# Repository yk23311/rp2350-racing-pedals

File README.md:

# 基于 RP2350 的赛车模拟器油门与刹车

**嘉立创打样资料**包括 [Gerber ZIP](hardware/jlc-v0.1/01-PCB-Gerber-RS274X.zip)、[SMT BOM](hardware/jlc-v0.1/02-BOM-SMT.csv)、[贴装坐标](hardware/jlc-v0.1/03-CPL-SMT.csv)和[下单说明](hardware/jlc-v0.1/README.md)。

**可扩展接线底板 V0.1**预留四路模拟端子、16 键、I²C 屏幕、面板编码器、震动控制和直驱接口子板槽。源码与针脚说明见 [KiCad 工程](hardware/carrier/README.md)，手焊见[材料清单、焊接手册和分区图](hardware/carrier-assembly-v0.1/README.md)。实板已用于双踏板测试，扩展接口仍需固件适配和上板验收。

**下载：[v0.4.0 预发布版](https://github.com/yk23311/rp2350-racing-pedals/releases/tag/v0.4.0)**，包含普通/诊断UF2、含GUI的源码包、快速说明与SHA256。软件测试通过，仍待实机验收；GUI源码包需Python环境。

**当前源码 0.6.0**支持 J1/J2 油门刹车互换、Xbox 桥接与原生 HID 方向盘切换，以及按键测试、震动测试和一键升级。Windows 已验证实板的三个独立方向盘轴，《地平线 6》的自定义方向盘布局保存仍待验证。 [操作与验证记录](docs/reports/25-simulator-wheel-handoff.md)

**新版驾驶控制中心已实现**：自动识别串口，实时踏板百分比、手柄按键/摇杆/扳机监视，踏板和手柄曲线预览与调参，手柄按钮→手柄/键盘映射。双击根目录 **启动调参GUI.bat**，详见[一步步使用说明](docs/control-center.md)。

按下文构建桥接固件，产物为 `dist/host/pedals-host.uf2`。Type-C 接电脑，2.4G 接收器插板卡 USB-A，踏板接底板 J1/J2。曲线和映射由板端执行，关闭 GUI 后仍有效。

旧固件可继续调踏板；手柄遥测和配置会明确显示不支持。新固件能迁移读取旧PDL1校准；显式保存后使用PDL2，旧固件不能读取新格式，降级前请备份校准。下文旧HID/Tk内容作为历史与兼容路线保留，最新入口为[HANDOFF.md](HANDOFF.md)。

**当前传感器仅确认 5V 供电，输出类型和电压未知。先按 [硬件接入说明](docs/hardware.md) 测量，不能直接把未知信号接到 GP26/GP27。** 未校准默认输出中立。

## 从 GitHub 首次使用

本仓库包含源码、测试、文档与界面演示图，不上传本地工具链、`.venv`、`build`、`deps`或`dist`。面向Windows与微雪RP2350-USB-A开发板；没有硬件也能预览GUI。

```powershell
python -m venv .venv
.\.venv\Scripts\python.exe -m pip install -r tools/requirements.txt
powershell -ExecutionPolicy Bypass -File tools/start_gui.ps1 -Demo
```

实际连接时去掉`-Demo`。先按下文构建桥接固件；旧固件首次需手动BOOT安装，此后可在GUI“固件升级”选择UF2并点击自动升级。GUI不会在后台自行刷机。界面如下（演示数据）：

## 工程入口

- [方案审核与来源](docs/reports/01-review.md)
- [首版设计](docs/superpowers/specs/2026-10-30-pedals-design.md) / [实施计划](docs/superpowers/plans/2026-10-30-pedals-plan.md)
- [步骤及交接报告总表](docs/reports/00-handoff.md)
- [硬件说明](docs/hardware.md) / [验收步骤](docs/validation.md) / [CDC协议](docs/protocol.md)

目录：`src/core/` 纯C算法、记录格式、控制台、USB报告布局与中立屏障；`firmware/` Pico HAL、Flash、TinyUSB、主循环；`tools/` 构建、CLI、GUI；`tests/` PC验证。

## 电脑端测试

Windows 已安装 Visual Studio C++/Clang、CMake、Ninja 和 Python 时：

```powershell
powershell -ExecutionPolicy Bypass -File tools/build_host.ps1
```

其他平台也可用原生C编译器运行：

```sh
cmake -S . -B build/host -DCMAKE_BUILD_TYPE=Release
cmake --build build/host
ctest --test-dir build/host --output-on-failure
python -m unittest discover -s tests -p 'test_*.py' -v
```

## 构建固件（Windows）

```powershell
python tools/fetch_deps.py
powershell -ExecutionPolicy Bypass -File tools/build_firmware.ps1 -UsbMode host
```

依赖只下载至项目 `deps/`：Pico SDK 2.2.0、其锁定的 TinyUSB、Arm GNU 14.3.rel1。下载较大；需要联网。脚本打印 SHA256 供记录，但不等于验证上游数字签名。桥接构建输出 `dist/host/pedals-host.*`；不传`-UsbMode host`时脚本仍默认构建独立踏板`dist/xinput/pedals-xinput.*`；`-UsbMode hid`输出 `dist/hid/pedals-hid.*`。UF2使用 SDK定义的 RP2350 ARM-S family，不自动烧录。

Windows Arm链接器在本项目中文路径下无法解析其标准库；脚本临时使用空闲R:映射本项目，完成或失败后移除。R:已被占用时可传入 `-DriveLetter S`；不会覆盖现有盘符，也不移动工程。构建缓存分为 `build/firmware-xinput-R/` 与 `build/firmware-hid-R/`。

Flash配置保留区：`0x101FE000` 和 `0x101FF000` 两个4KiB扇区；正常程序链接区不覆盖该区域。更新固件通常保留配置；整片擦除会清空。

## 上板后调参

项目已准备好独立的 `.venv` 串口环境；GUI 使用 Python 自带的 Tkinter，无需 PyQt。

**最简单的启动方式：双击项目根目录的 `启动调参GUI.bat`。** 也可以在 PowerShell 中运行：

```powershell
powershell -ExecutionPolicy Bypass -File tools/start_gui.ps1
```

只想检查环境而不打开窗口：

```powershell
powershell -ExecutionPolicy Bypass -File tools/start_gui.ps1 -Check
```

移交到新电脑时先执行 `python -m venv .venv`，再执行 `.\.venv\Scripts\python.exe -m pip install -r tools/requirements.txt`。CLI也使用该虚拟环境的Python；下列示例运行前可执行 `.\.venv\Scripts\Activate.ps1`，或把 `python` 换成 `.\.venv\Scripts\python.exe`。

输入设备管理器中确认的串口号。滑条调节后点“应用参数”在 RAM 生效；松开两踏板并回零后点“保存到 Flash”。两轴分别执行“全松开：开始校准”→“踩到底并保持：完成”，每个位置至少保持100ms再操作。

也可使用CLI（以下COM5仅作示例）：

```powershell
python tools/pedalctl.py --port COM5 get
python tools/pedalctl.py --port COM5 calibrate 0
python tools/pedalctl.py --port COM5 calibrate 1
python tools/pedalctl.py --port COM5 set 1 --on 300 --off 100 --gamma 200 --window 4
python tools/pedalctl.py --port COM5 save
python tools/pedalctl.py --port COM5 export pedal-config.json
python tools/pedalctl.py --port COM5 monitor --seconds 3600 --interval 0.1 --output aging.csv
```

`on/off`单位为万分之一（300=3%），`gamma`单位为百分之一（200=2.00）。`SAVE`返回状态错误时先松开两踏板、结束校准、等待中立报告完成再重试；不能视作已经保存。CSV为电脑轮询数据，默认10Hz，不是全部1kHz ADC样本。

## 已明确的限制

- 当前为开发验证版本；实机验收记录见交接总表。标准HID不等于XInput，按目标游戏验证兼容性。
- 开发 VID/PID 为 `CAFE:4011`，不作为正式分配的产品身份；发布硬件前需获得合适的USB身份并复验描述符。
- 固件声明最大100mA USB总电流，连接传感器前确认整板与传感器总需求；不在此供电预算内接电机。
- 方向盘模式支持输入。屏幕菜单、底板外置震动马达和伺服力反馈仍需适配。

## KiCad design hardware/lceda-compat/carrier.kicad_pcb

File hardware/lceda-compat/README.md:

# 嘉立创EDA网络兼容导入候选包

2026-11-07。这个目录仍是**用于导入的KiCad格式兼容副本，不是已生成的EDA原生eprj/epro工程**。原始 `hardware/carrier` 和已经核验的Gerber包保持不变。

## 为什么另做这个包

用户导出的`eda-import-diff.csv`表明：221个实际连接的引脚，在当前EDA PCB中导入前均显示为未指定网络；49个GND引脚在原理图侧被PWR_FLAG命名；另有15处元件值回填差异。原始KiCad10板图使用新版具名网络语法，旧式索引语法是本次兼容候选的验证方向。只显示铜线/DRC条数减少，不能证明网络导入成功。

## 副本中的兼容处理

- 所有844处网络关联写为旧式数字索引，补齐网络表；pad保留索引和原网名，segment/via/铜区引用索引，铜区增加net_name。**文件版本没有伪改为旧版。**
- 每个封装的Reference/Value属性使用兼容fp_text形式表达，保留各自数值、坐标、字体、隐藏状态和UUID。
- 仅移除原理图ERC专用PWR_FLAG及其独立标记支线/标签，从而避免EDA把这个声明当作地网名称；模块GND引脚的ERC类型从power_in调整为power_out，承担原来的供电声明，实体连接不变。本地模块符号库同步此纯ERC元数据变化。
- 581段走线、27个过孔、72个元件、238个焊盘、安装孔/禁布区和其他PCB几何均保留。

## 已完成的验证

- 原生KiCad读回全部元件/焊盘/走线/过孔，与原件逐项比较，几何/网络/实际值一致。
- 原生ERC：0违规；DRC：0违规、0未连接、0原理图一致性问题，使用同一原规则配置。
- 原生导出的原理图网表和原72元件电气模型逐脚一致。
- 九层Gerber的完整绘图流与原版完全一致；PTH/NPTH钻孔指令与原版一致。
- Python全套130项测试通过，其中6项为新增兼容合同测试。
- 独立复核反向还原全部PCB变换后，其完整S表达式结构与原版一致；符号/原理图只存在上述声明变化。

报告保存在`reports/`；诊断源报告UTF-16、制表符分隔，虽然后缀为CSV，不能按普通逗号CSV解析。

## 用户手动验证步骤

1. 在EDA专业版开始页选“导入KiCad”，选择`carrier-net-compat.zip`，导入为新工程。
2. 首次先查看PCB，不执行“导入更新”或重建铺铜。任选有连接的焊盘，查看网络属性是否已正确获得名字，例如C1.1为ADC_THROTTLE、C1.2为GND（显示时可能带层级前缀），R25应为4.7k、C7应为4.7µF。
3. 运行DRC并保留结果。如果仍有网表差异，只查看/导出差异报告，不盲目应用；报告中221项网络都从未指定开始的情况应先排除。
4. 确认原生网络已经保留后，再按实际错误匹配最小孔径0.30mm规则，并验证重建铺铜后铜线和连接状态仍保留。

**上述EDA实际导入、属性/网络保留、铺铜重建和EDA DRC均尚待用户验证。** 不得直接把本候选包作为已完成EDA验收的生产稿，不保证满足EDA专用优惠券资格。原始已核验Gerber仍是独立制造入口。

生成器为`tools/hardware/prepare_lceda_compat.py`，默认只生成副本；重新生成后必须重新运行原生检查和等价比对再打包，不沿用旧验证结论。

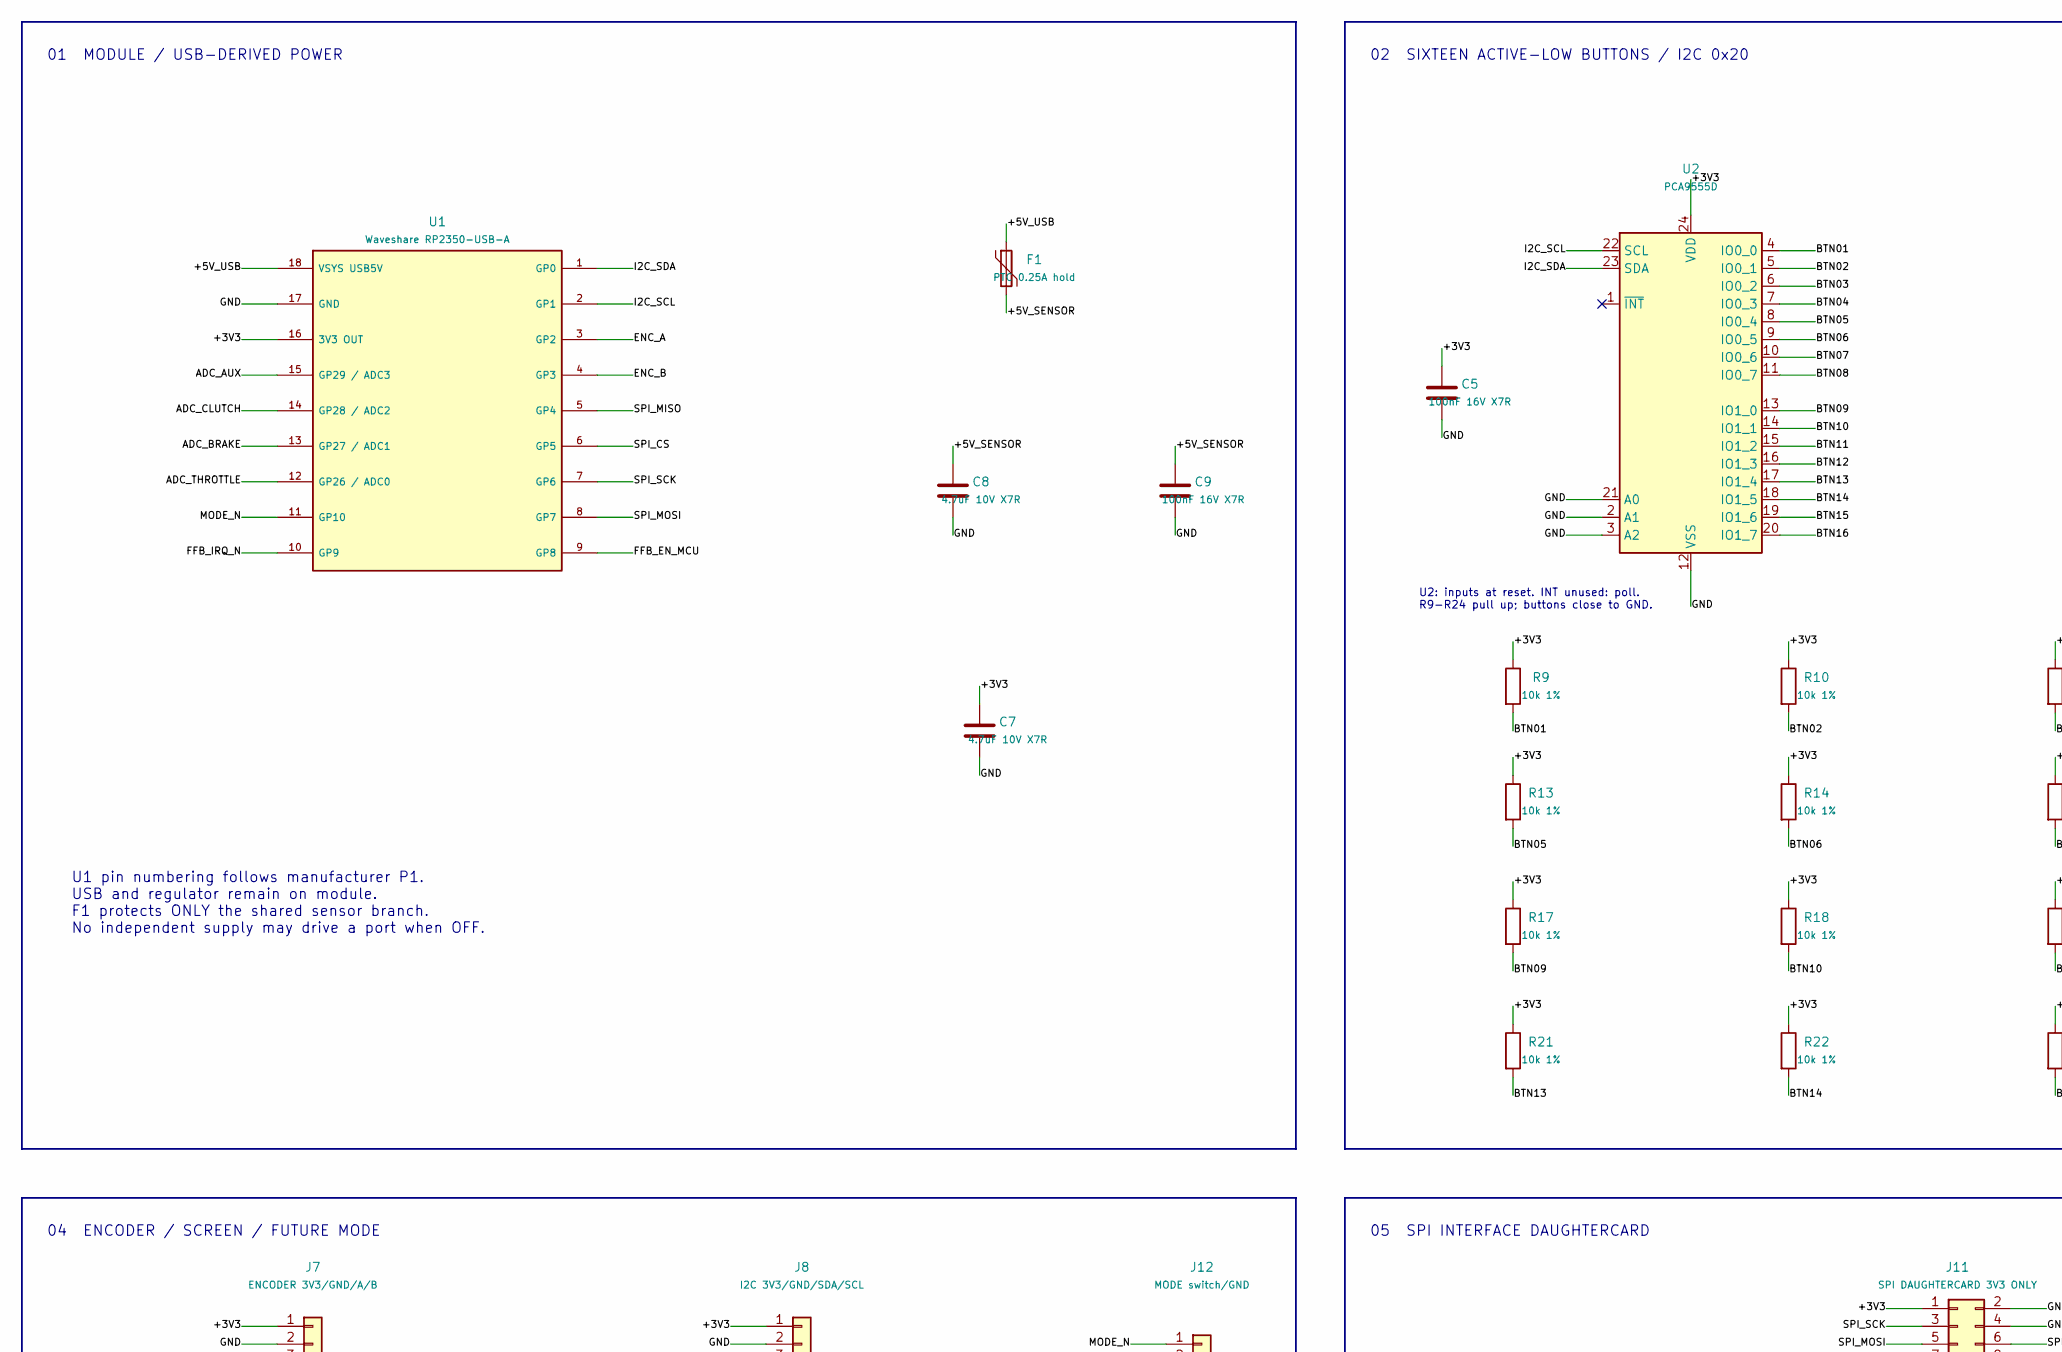
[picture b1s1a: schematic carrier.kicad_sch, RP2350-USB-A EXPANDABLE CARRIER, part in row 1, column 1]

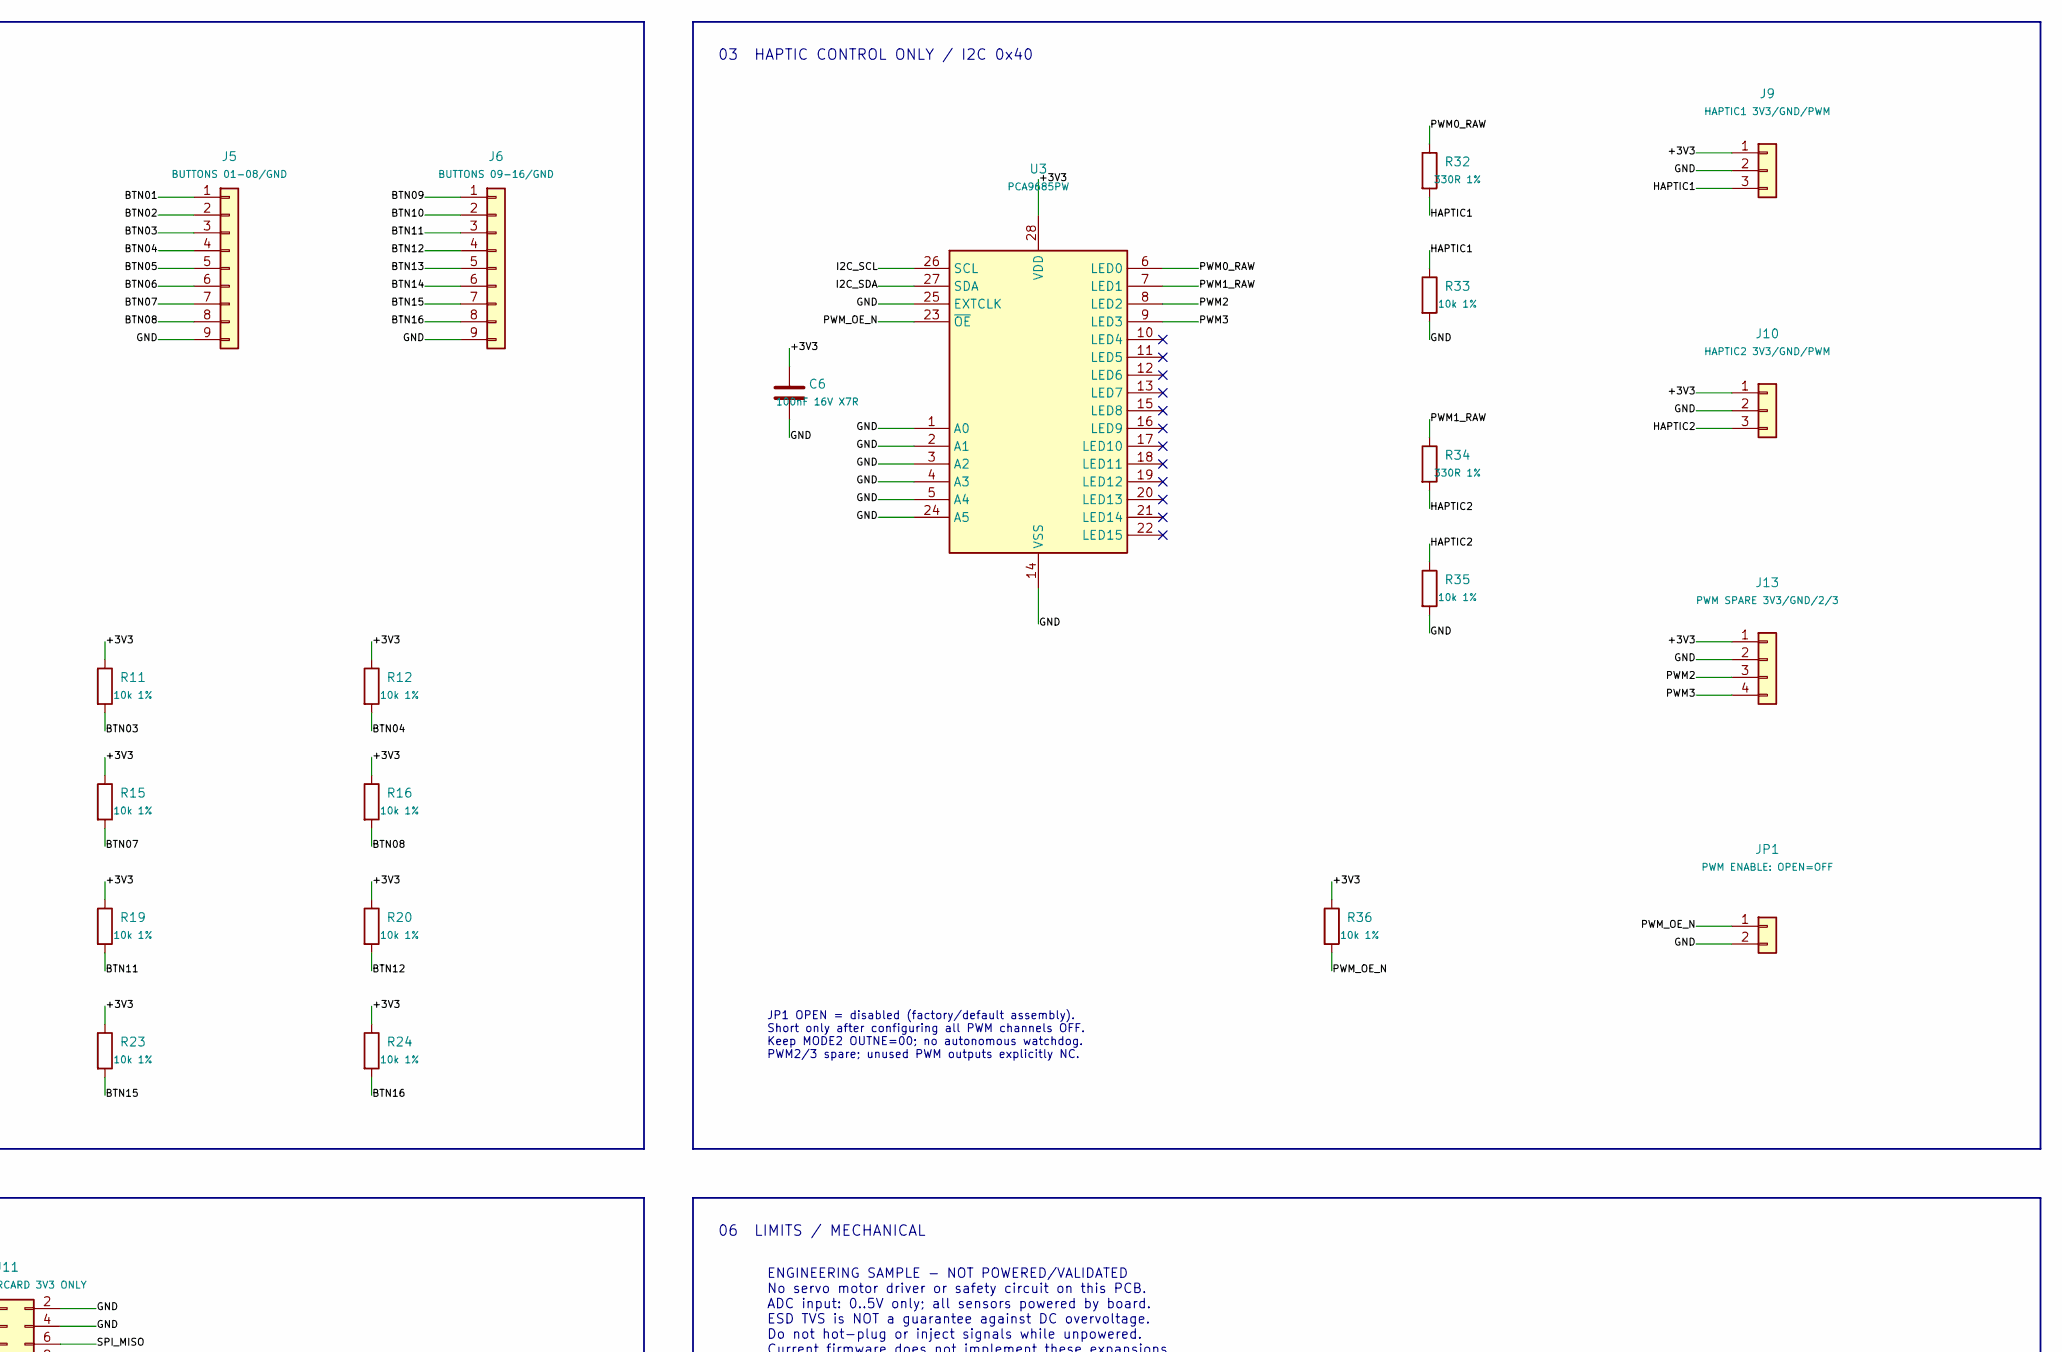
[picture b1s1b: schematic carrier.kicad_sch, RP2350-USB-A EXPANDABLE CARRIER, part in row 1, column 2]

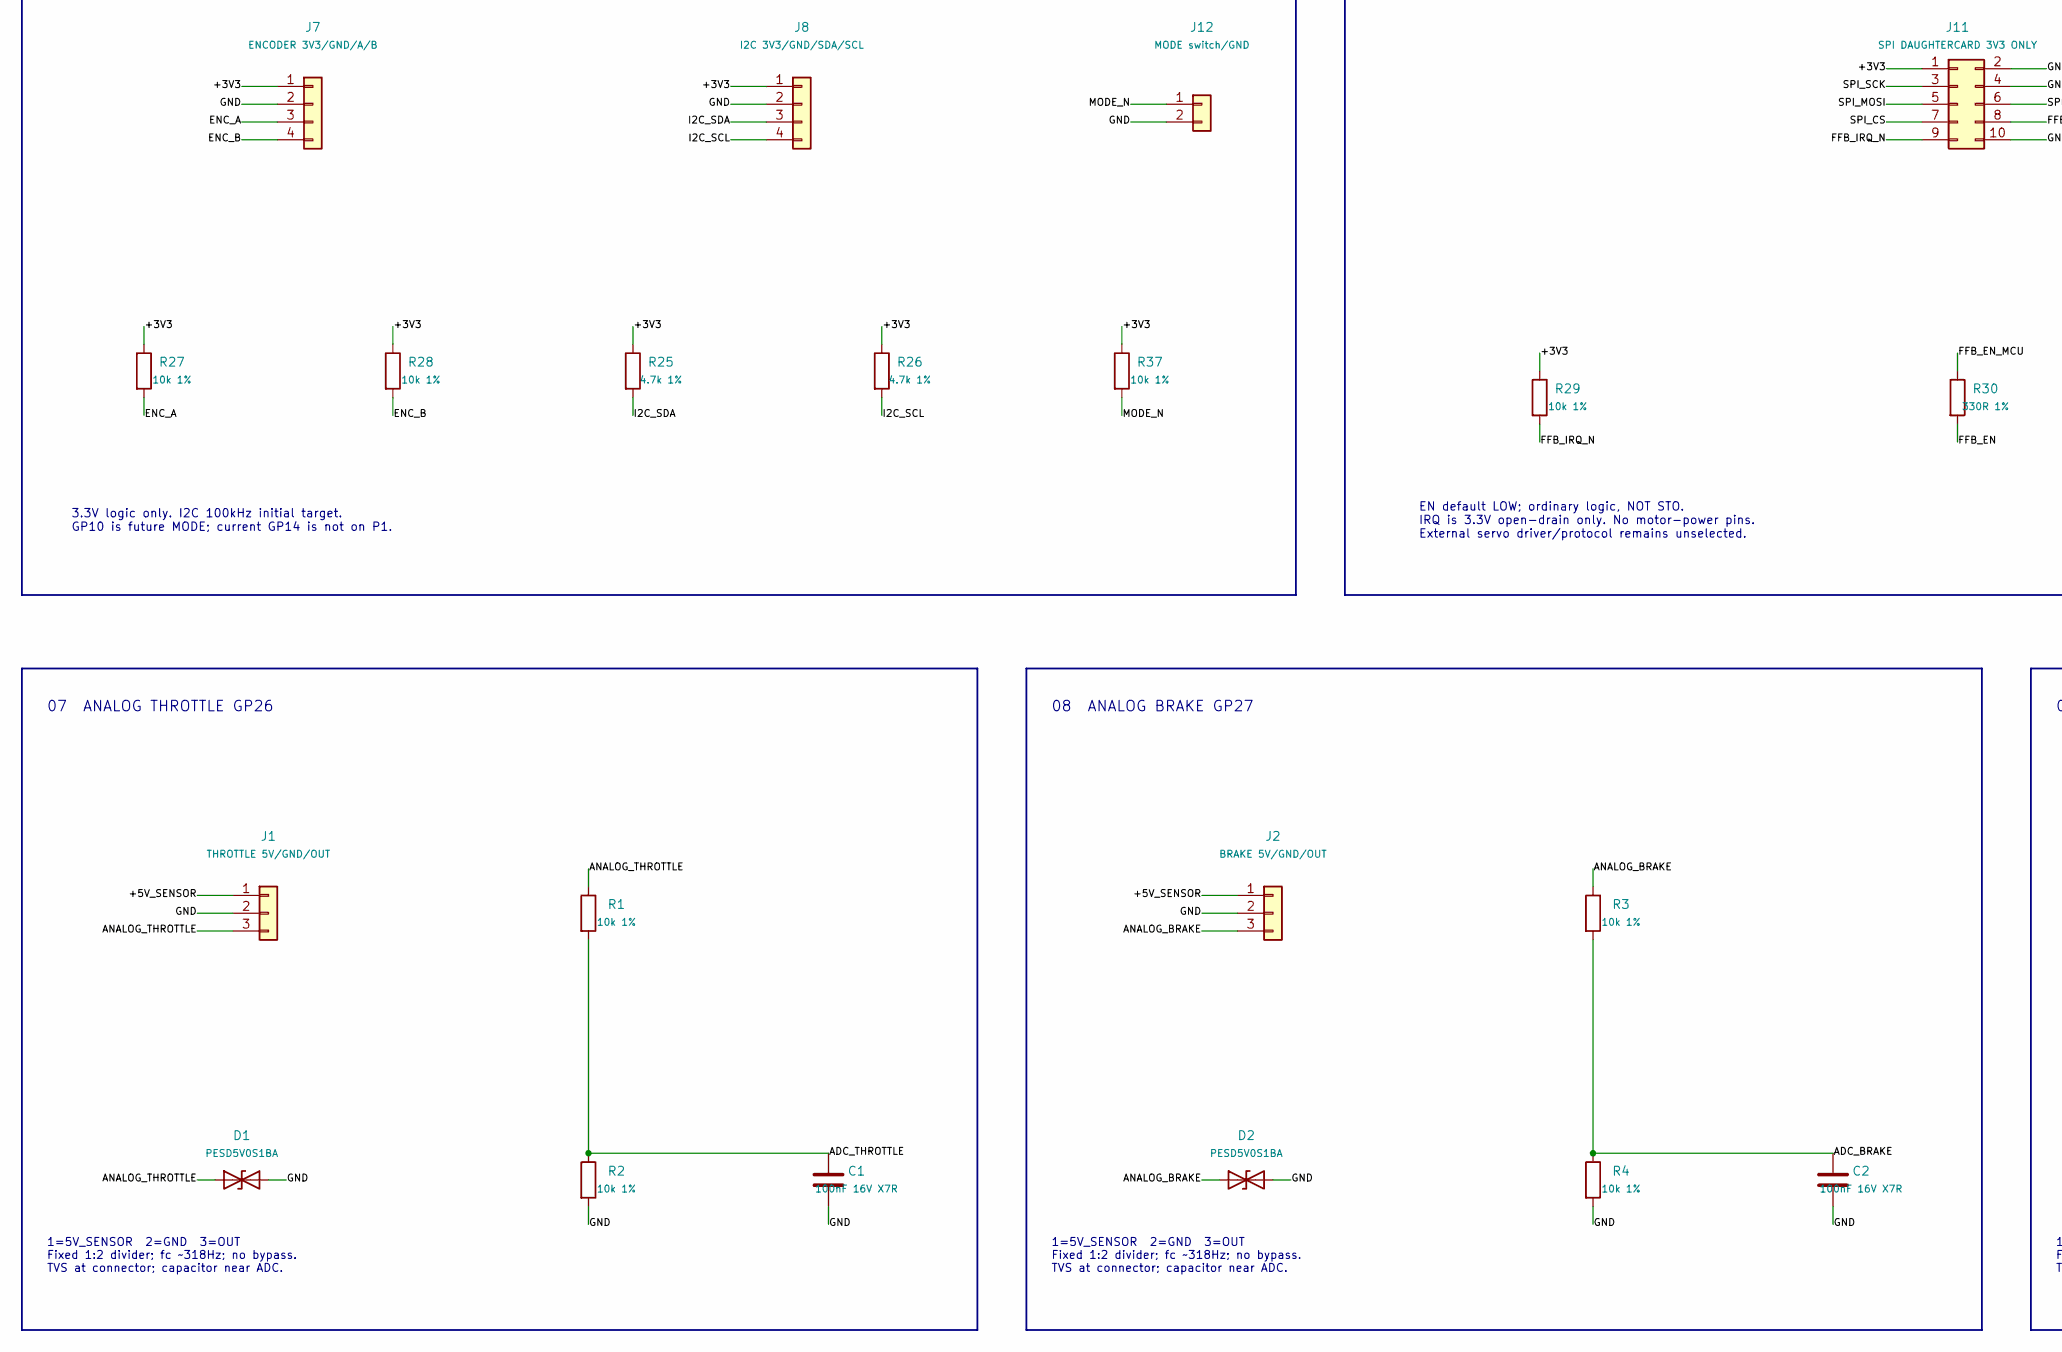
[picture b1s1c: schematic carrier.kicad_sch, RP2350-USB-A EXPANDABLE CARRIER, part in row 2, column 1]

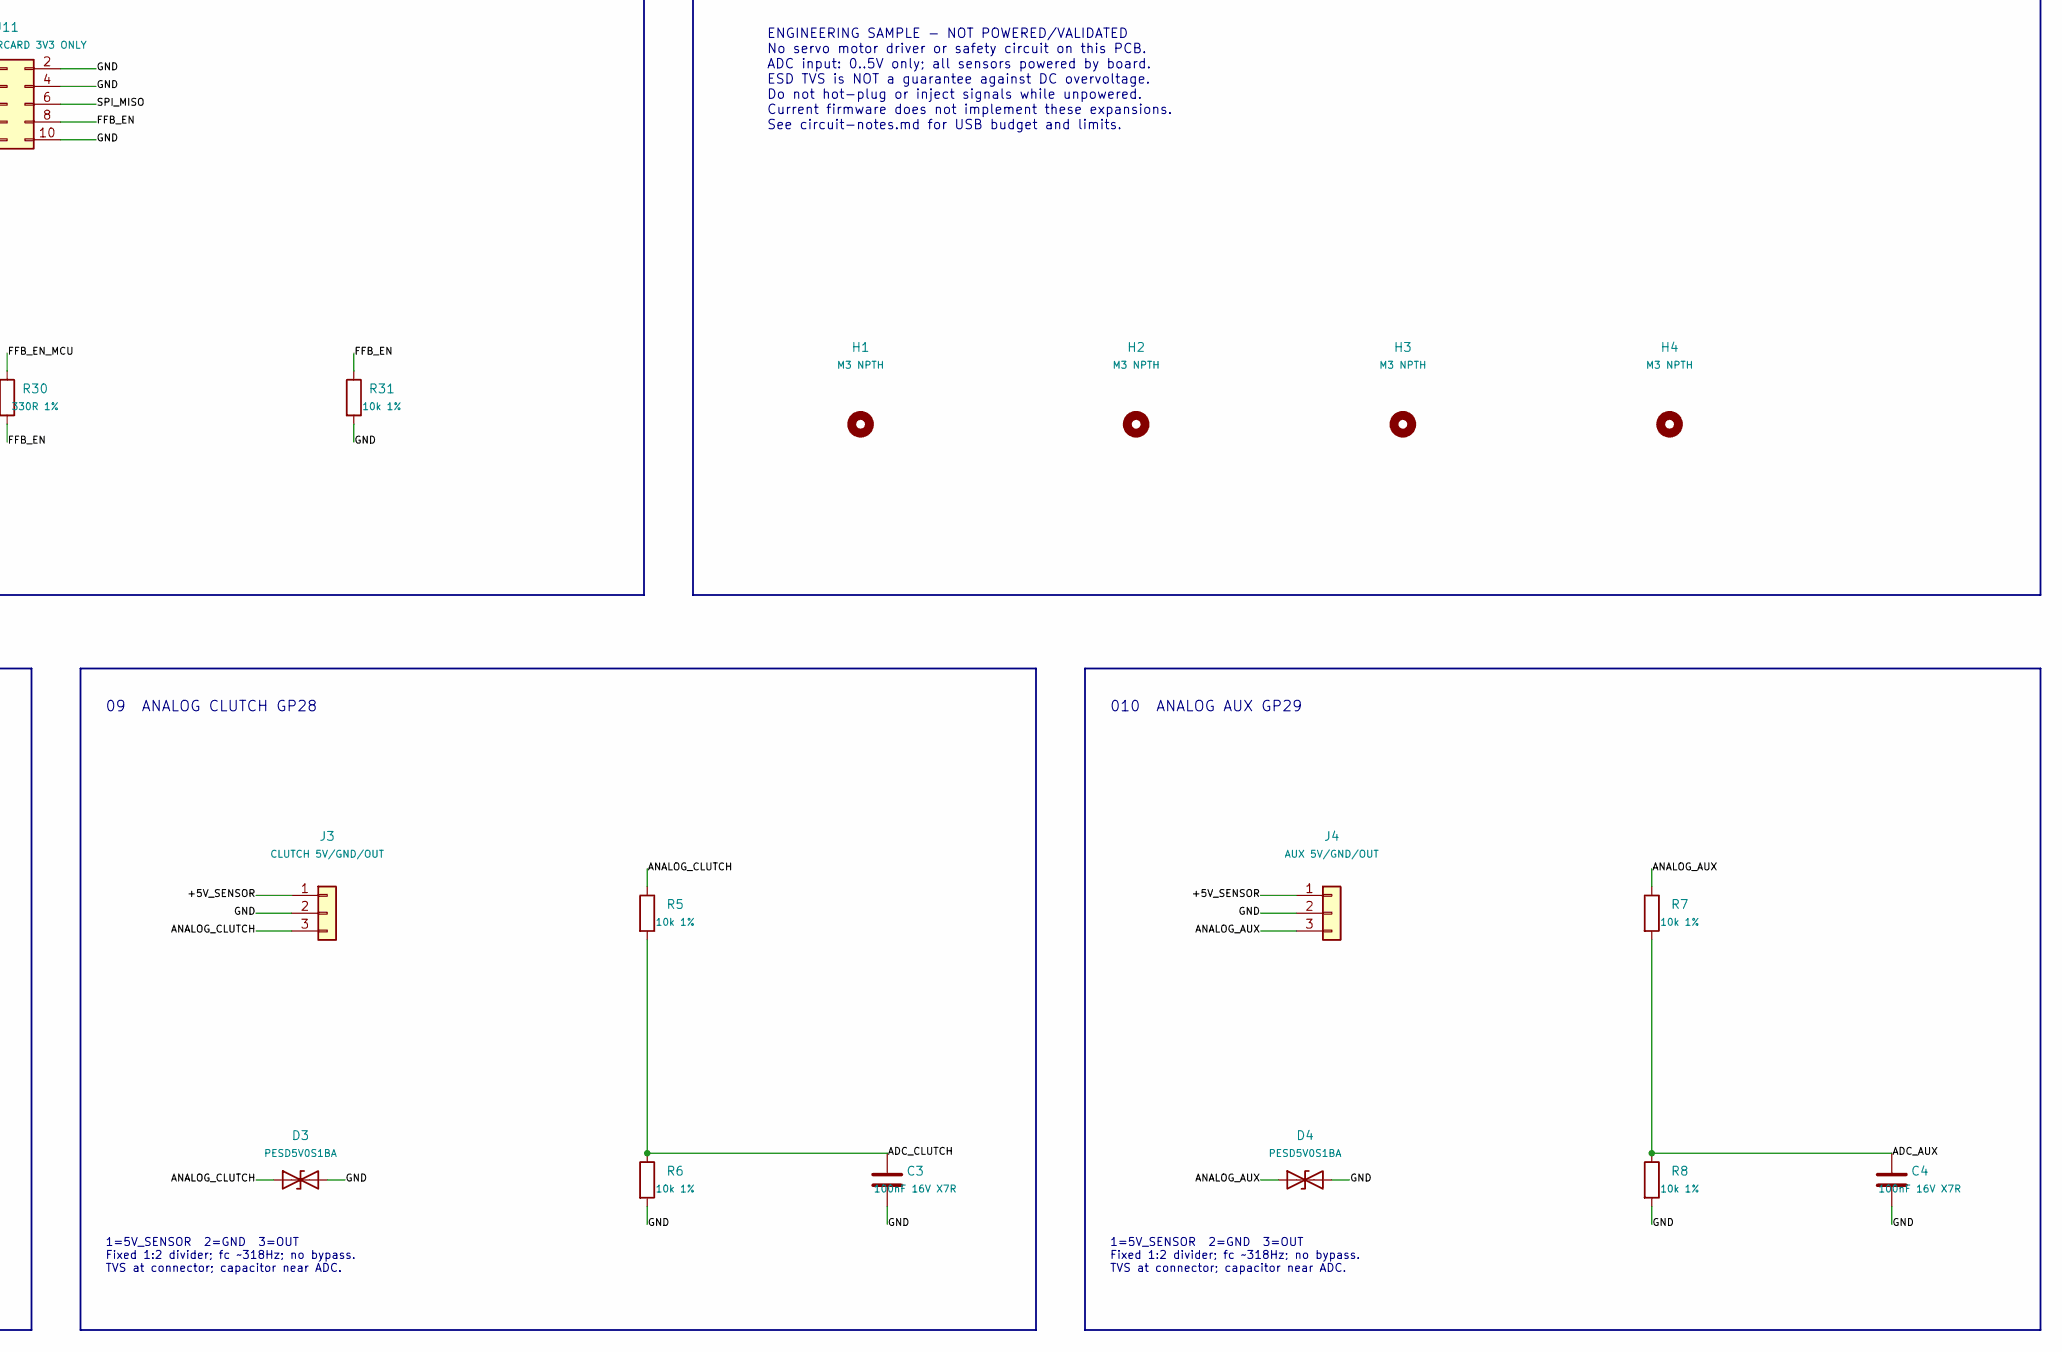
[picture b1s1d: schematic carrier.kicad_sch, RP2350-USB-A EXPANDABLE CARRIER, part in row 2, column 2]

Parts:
C1, C2, C3, C4, C5, C6, C9: 100nF 16V X7R; C_0805_2012Metric
C7, C8: 4.7uF 10V X7R; C_0805_2012Metric
D1, D2, D3, D4: PESD5V0S1BA; D_SOD-323
F1: PTC 0.25A hold; Fuse_1206_3216Metric
H1, H2, H3, H4: M3 NPTH; MountingHole_3.2mm_M3
J1: THROTTLE 5V/GND/OUT; TerminalBlock_Phoenix_MKDS-1,5-3-5.08_1x03_P5.08mm_Horizont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
J2: BRAKE 5V/GND/OUT; TerminalBlock_Phoenix_MKDS-1,5-3-5.08_1x03_P5.08mm_Horizont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
J3: CLUTCH 5V/GND/OUT; TerminalBlock_Phoenix_MKDS-1,5-3-5.08_1x03_P5.08mm_Horizont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
J4: AUX 5V/GND/OUT; TerminalBlock_Phoenix_MKDS-1,5-3-5.08_1x03_P5.08mm_Horizont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
J5: BUTTONS 01-08/GND; PinHeader_1x09_P2.54mm_Vertical
J6: BUTTONS 09-16/GND; PinHeader_1x09_P2.54mm_Vertical
J7: ENCODER 3V3/GND/A/B; PinHeader_1x04_P2.54mm_Vertical
J8: I2C 3V3/GND/SDA/SCL; PinHeader_1x04_P2.54mm_Vertical
J9: HAPTIC1 3V3/GND/PWM; PinHeader_1x03_P2.54mm_Vertical
J10: HAPTIC2 3V3/GND/PWM; PinHeader_1x03_P2.54mm_Vertical
J11: SPI DAUGHTERCARD 3V3 ONLY; PinHeader_2x05_P2.54mm_Vertical
J12: MODE switch/GND; PinHeader_1x02_P2.54mm_Vertical
J13: PWM SPARE 3V3/GND/2/3; PinHeader_1x04_P2.54mm_Vertical
JP1: PWM ENABLE: OPEN=OFF; PinHeader_1x02_P2.54mm_Vertical
R1, R2, R3, R4, R5, R6, R7, R8, R9, R10, R11, R12, R13, R14, R15, R16, R17, R18, R19, R20, R21, R22, R23, R24, R27, R28, R29, R31, R33, R35, R36, R37: 10k 1%; R_0805_2012Metric
R25, R26: 4.7k 1%; R_0805_2012Metric
R30, R32, R34: 330R 1%; R_0805_2012Metric
U1: Waveshare RP2350-USB-A; Waveshare_RP2350_USB_A
U2: PCA9555D; SOIC-24W_7.5x15.4mm_P1.27mm
U3: PCA9685PW; TSSOP-28_4.4x9.7mm_P0.65mm

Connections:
/+3V3: C5.1, C6.1, C7.1, J7.1, J8.1, J9.1, J10.1, J11.1, J13.1, R9.1, R10.1, R11.1, R12.1, R13.1, R14.1, R15.1, R16.1, R17.1, R18.1, R19.1, R20.1, R21.1, R22.1, R23.1, R24.1, R25.1, R26.1, R27.1, R28.1, R29.1, R36.1, R37.1, U1.16 (3V3 OUT), U2.24 (VDD), U3.28 (VDD)
/+5V_SENSOR: C8.1, C9.1, F1.2, J1.1, J2.1, J3.1, J4.1
/+5V_USB: F1.1, U1.18 (VSYS USB5V)
/ADC_AUX: C4.1, R7.2, R8.1, U1.15 (GP29 / ADC3)
/ADC_BRAKE: C2.1, R3.2, R4.1, U1.13 (GP27 / ADC1)
/ADC_CLUTCH: C3.1, R5.2, R6.1, U1.14 (GP28 / ADC2)
/ADC_THROTTLE: C1.1, R1.2, R2.1, U1.12 (GP26 / ADC0)
/ANALOG_AUX: D4.1 (A1), J4.3, R7.1
/ANALOG_BRAKE: D2.1 (A1), J2.3, R3.1
/ANALOG_CLUTCH: D3.1 (A1), J3.3, R5.1
/ANALOG_THROTTLE: D1.1 (A1), J1.3, R1.1
/BTN01: J5.1, R9.2, U2.4 (IO0_0)
/BTN02: J5.2, R10.2, U2.5 (IO0_1)
/BTN03: J5.3, R11.2, U2.6 (IO0_2)
/BTN04: J5.4, R12.2, U2.7 (IO0_3)
/BTN05: J5.5, R13.2, U2.8 (IO0_4)
/BTN06: J5.6, R14.2, U2.9 (IO0_5)
/BTN07: J5.7, R15.2, U2.10 (IO0_6)
/BTN08: J5.8, R16.2, U2.11 (IO0_7)
/BTN09: J6.1, R17.2, U2.13 (IO1_0)
/BTN10: J6.2, R18.2, U2.14 (IO1_1)
/BTN11: J6.3, R19.2, U2.15 (IO1_2)
/BTN12: J6.4, R20.2, U2.16 (IO1_3)
/BTN13: J6.5, R21.2, U2.17 (IO1_4)
/BTN14: J6.6, R22.2, U2.18 (IO1_5)
/BTN15: J6.7, R23.2, U2.19 (IO1_6)
/BTN16: J6.8, R24.2, U2.20 (IO1_7)
/ENC_A: J7.3, R27.2, U1.3 (GP2)
/ENC_B: J7.4, R28.2, U1.4 (GP3)
/FFB_EN: J11.8, R30.2, R31.1
/FFB_EN_MCU: R30.1, U1.9 (GP8)
/FFB_IRQ_N: J11.9, R29.2, U1.10 (GP9)
/GND: C1.2, C2.2, C3.2, C4.2, C5.2, C6.2, C7.2, C8.2, C9.2, D1.2 (A2), D2.2 (A2), D3.2 (A2), D4.2 (A2), J1.2, J2.2, J3.2, J4.2, J5.9, J6.9, J7.2, J8.2, J9.2, J10.2, J11.2, J11.4, J11.10, J12.2, J13.2, JP1.2, R2.2, R4.2, R6.2, R8.2, R31.2, R33.2, R35.2, U1.17 (GND), U2.2 (A1), U2.3 (A2), U2.12 (VSS), U2.21 (A0), U3.1 (A0), U3.2 (A1), U3.3 (A2), U3.4 (A3), U3.5 (A4), U3.14 (VSS), U3.24 (A5), U3.25 (EXTCLK)
/HAPTIC1: J9.3, R32.2, R33.1
/HAPTIC2: J10.3, R34.2, R35.1
/I2C_SCL: J8.4, R26.2, U1.2 (GP1), U2.22 (SCL), U3.26 (SCL)
/I2C_SDA: J8.3, R25.2, U1.1 (GP0), U2.23 (SDA), U3.27 (SDA)
/MODE_N: J12.1, R37.2, U1.11 (GP10)
/PWM0_RAW: R32.1, U3.6 (LED0)
/PWM1_RAW: R34.1, U3.7 (LED1)
/PWM2: J13.3, U3.8 (LED2)
/PWM3: J13.4, U3.9 (LED3)
/PWM_OE_N: JP1.1, R36.2, U3.23 (~OE)
/SPI_CS: J11.7, U1.6 (GP5)
/SPI_MISO: J11.6, U1.5 (GP4)
/SPI_MOSI: J11.5, U1.8 (GP7)
/SPI_SCK: J11.3, U1.7 (GP6)

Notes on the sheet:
01 MODULE / USB-DERIVED POWER
02 SIXTEEN ACTIVE-LOW BUTTONS / I2C 0x20
03 HAPTIC CONTROL ONLY / I2C 0x40
04 ENCODER / SCREEN / FUTURE MODE
05 SPI INTERFACE DAUGHTERCARD
06 LIMITS / MECHANICAL
U1 pin numbering follows manufacturer P1. USB and regulator remain on module. F1 protects ONLY the shared sensor branch. No independent supply may drive a port when OFF.
U2: inputs at reset. INT unused: poll. R9-R24 pull up; buttons close to GND.
JP1 OPEN = disabled (factory/default assembly). Short only after configuring all PWM channels OFF. Keep MODE2 OUTNE=00; no autonomous watchdog. PWM2/3 spare; unused PWM outputs explicitly NC.
3.3V logic only. I2C 100kHz initial target. GP10 is future MODE; current GP14 is not on P1.
EN default LOW; ordinary logic, NOT STO. IRQ is 3.3V open-drain only. No motor-power pins. External servo driver/protocol remains unselected.
ENGINEERING SAMPLE - NOT POWERED/VALIDATED No servo motor driver or safety circuit on this PCB. ADC input: 0..5V only; all sensors powered by board. ESD TVS is NOT a guarantee against DC overvoltage. Do not hot-plug or inject signals while unpowered. Current firmware does not implement these expans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
07 ANALOG THROTTLE GP26
1=5V_SENSOR 2=GND 3=OUT Fixed 1:2 divider; fc ~318Hz; no bypass. TVS at connector; capacitor near ADC.
08 ANALOG BRAKE GP27
09 ANALOG CLUTCH GP28
010 ANALOG AUX GP29

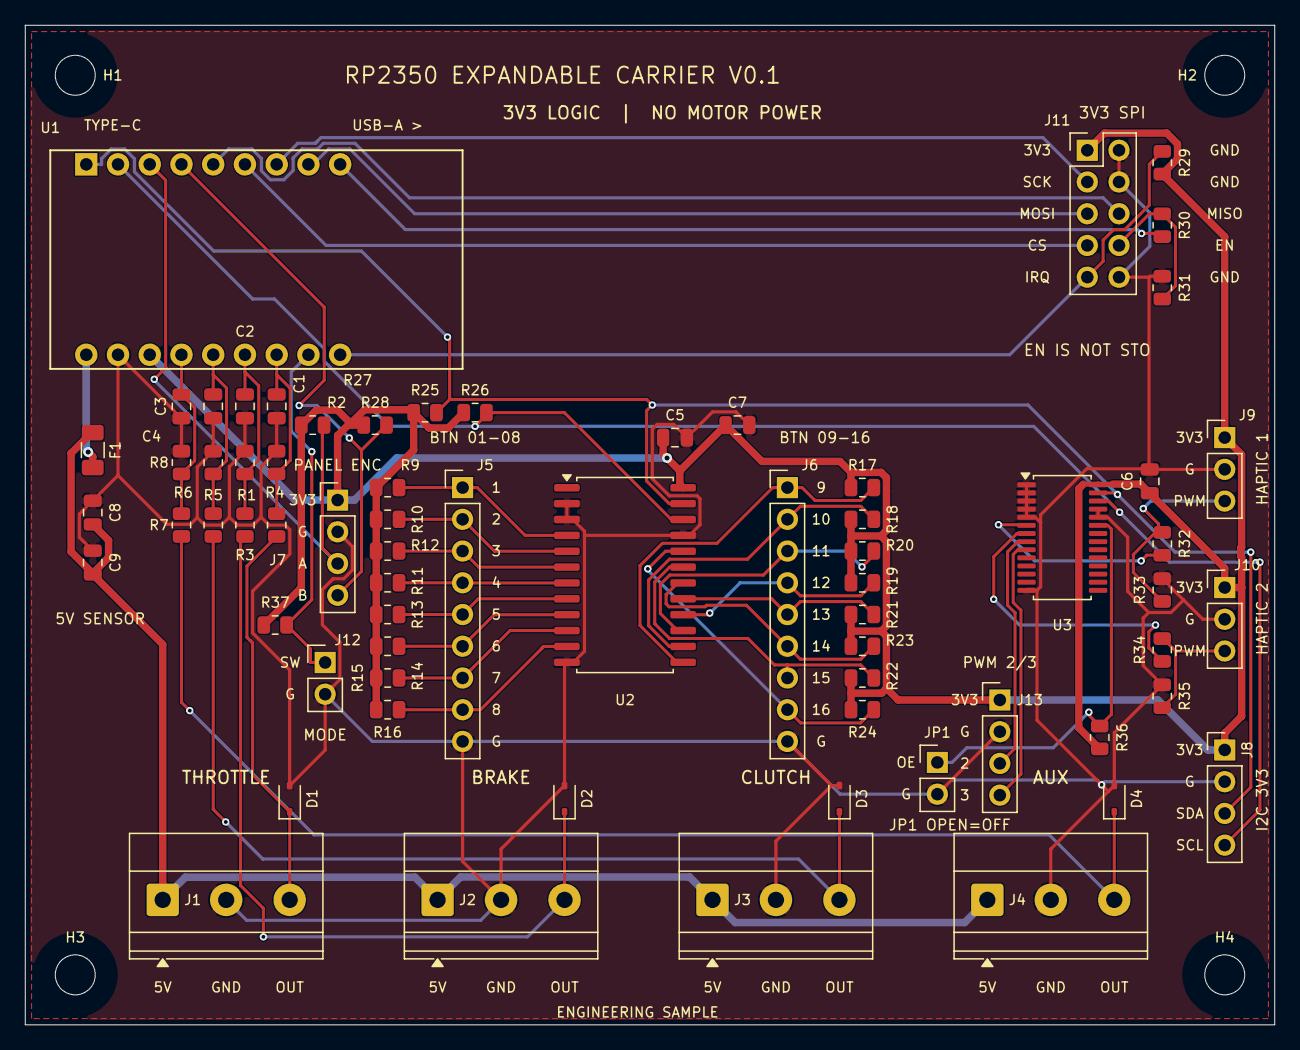
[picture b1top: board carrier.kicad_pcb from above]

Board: 2 copper layers, 100.0 x 80.0 mm, 72 parts (0 on the bottom side), 47 nets.

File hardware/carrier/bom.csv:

Reference,Value,Footprint,Manufacturer,MPN,Purpose,Assembly
U1,Waveshare RP2350-USB-A,Carrier:Waveshare_RP2350_USB_A,,Waveshare RP2350-USB-A,Plug-in USB controller module,"Two 1x09 2.54mm female sockets, 15.24mm row spacing; then plug module into sockets"
U2,PCA9555D,Package_SO:SOIC-24W_7.5x15.4mm_P1.27mm,NXP,"PCA9555D,118",16 active-low buttons; poll over I2C,Fit
U3,PCA9685PW,Package_SO:TSSOP-28_4.4x9.7mm_P0.65mm,NXP,"PCA9685PW,118",Two haptic PWM signals; two spare,Fit
J1,THROTTLE 5V/GND/OUT,"TerminalBlock_Phoenix:TerminalBlock_Phoenix_MKDS-1,5-3-5.08_1x03_P5.08mm_Horizontal",,Phoenix Contact 1715734,0..5V analog sensor only,Fit
R1,10k 1%,Resistor_SMD:R_0805_2012Metric,,,Divider upper arm; no bypass,Fit
R2,10k 1%,Resistor_SMD:R_0805_2012Metric,,,Divider lower arm,Fit
C1,100nF 16V X7R,Capacitor_SMD:C_0805_2012Metric,,,ADC low-pass 318 Hz nominal,Fit
D1,PESD5V0S1BA,Diode_SMD:D_SOD-323,Nexperia,"PESD5V0S1BA,115",Connector ESD shunt; not DC overvoltage protection,Fit
J2,BRAKE 5V/GND/OUT,"TerminalBlock_Phoenix:TerminalBlock_Phoenix_MKDS-1,5-3-5.08_1x03_P5.08mm_Horizontal",,Phoenix Contact 1715734,0..5V analog sensor only,Fit
R3,10k 1%,Resistor_SMD:R_0805_2012Metric,,,Divider upper arm; no bypass,Fit
R4,10k 1%,Resistor_SMD:R_0805_2012Metric,,,Divider lower arm,Fit
C2,100nF 16V X7R,Capacitor_SMD:C_0805_2012Metric,,,ADC low-pass 318 Hz nominal,Fit
D2,PESD5V0S1BA,Diode_SMD:D_SOD-323,Nexperia,"PESD5V0S1BA,115",Connector ESD shunt; not DC overvoltage protection,Fit
J3,CLUTCH 5V/GND/OUT,"TerminalBlock_Phoenix:TerminalBlock_Phoenix_MKDS-1,5-3-5.08_1x03_P5.08mm_Horizontal",,Phoenix Contact 1715734,0..5V analog sensor only,Fit
R5,10k 1%,Resistor_SMD:R_0805_2012Metric,,,Divider upper arm; no bypass,Fit
R6,10k 1%,Resistor_SMD:R_0805_2012Metric,,,Divider lower arm,Fit
C3,100nF 16V X7R,Capacitor_SMD:C_0805_2012Metric,,,ADC low-pass 318 Hz nominal,Fit
D3,PESD5V0S1BA,Diode_SMD:D_SOD-323,Nexperia,"PESD5V0S1BA,115",Connector ESD shunt; not DC overvoltage protection,Fit
J4,AUX 5V/GND/OUT,"TerminalBlock_Phoenix:TerminalBlock_Phoenix_MKDS-1,5-3-5.08_1x03_P5.08mm_Horizontal",,Phoenix Contact 1715734,0..5V analog sensor only,Fit
R7,10k 1%,Resistor_SMD:R_0805_2012Metric,,,Divider upper arm; no bypass,Fit
R8,10k 1%,Resistor_SMD:R_0805_2012Metric,,,Divider lower arm,Fit
C4,100nF 16V X7R,Capacitor_SMD:C_0805_2012Metric,,,ADC low-pass 318 Hz nominal,Fit
D4,PESD5V0S1BA,Diode_SMD:D_SOD-323,Nexperia,"PESD5V0S1BA,115",Connector ESD shunt; not DC overvoltage protection,Fit
J5,BUTTONS 01-08/GND,Connector_PinHeader_2.54mm:PinHeader_1x09_P2.54mm_Vertical,,,,Fit
J6,BUTTONS 09-16/GND,Connector_PinHeader_2.54mm:PinHeader_1x09_P2.54mm_Vertical,,,,Fit
R9,10k 1%,Resistor_SMD:R_0805_2012Metric,,,External pull-up; switch to GND,Fit
R10,10k 1%,Resistor_SMD:R_0805_2012Metric,,,External pull-up; switch to GND,Fit
R11,10k 1%,Resistor_SMD:R_0805_2012Metric,,,External pull-up; switch to GND,Fit
R12,10k 1%,Resistor_SMD:R_0805_2012Metric,,,External pull-up; switch to GND,Fit
R13,10k 1%,Resistor_SMD:R_0805_2012Metric,,,External pull-up; switch to GND,Fit
R14,10k 1%,Resistor_SMD:R_0805_2012Metric,,,External pull-up; switch to GND,Fit
R15,10k 1%,Resistor_SMD:R_0805_2012Metric,,,External pull-up; switch to GND,Fit
R16,10k 1%,Resistor_SMD:R_0805_2012Metric,,,External pull-up; switch to GND,Fit
R17,10k 1%,Resistor_SMD:R_0805_2012Metric,,,External pull-up; switch to GND,Fit
R18,10k 1%,Resistor_SMD:R_0805_2012Metric,,,External pull-up; switch to GND,Fit
R19,10k 1%,Resistor_SMD:R_0805_2012Metric,,,External pull-up; switch to GND,Fit
R20,10k 1%,Resistor_SMD:R_0805_2012Metric,,,External pull-up; switch to GND,Fit
R21,10k 1%,Resistor_SMD:R_0805_2012Metric,,,External pull-up; switch to GND,Fit
R22,10k 1%,Resistor_SMD:R_0805_2012Metric,,,External pull-up; switch to GND,Fit
R23,10k 1%,Resistor_SMD:R_0805_2012Metric,,,External pull-up; switch to GND,Fit
R24,10k 1%,Resistor_SMD:R_0805_2012Metric,,,External pull-up; switch to GND,Fit
J7,ENCODER 3V3/GND/A/B,Connector_PinHeader_2.54mm:PinHeader_1x04_P2.54mm_Vertical,,,,Fit
J8,I2C 3V3/GND/SDA/SCL,Connector_PinHeader_2.54mm:PinHeader_1x04_P2.54mm_Vertical,,,,Fit
J9,HAPTIC1 3V3/GND/PWM,Connector_PinHeader_2.54mm:PinHeader_1x03_P2.54mm_Vertical,,,,Fit
J10,HAPTIC2 3V3/GND/PWM,Connector_PinHeader_2.54mm:PinHeader_1x03_P2.54mm_Vertical,,,,Fit
J11,SPI DAUGHTERCARD 3V3 ONLY,Connector_PinHeader_2.54mm:PinHeader_2x05_P2.54mm_Vertical,,,,Fit
J12,MODE switch/GND,Connector_PinHeader_2.54mm:PinHeader_1x02_P2.54mm_Vertical,,,,Fit
J13,PWM SPARE 3V3/GND/2/3,Connector_PinHeader_2.54mm:PinHeader_1x04_P2.54mm_Vertical,,,,Fit
JP1,PWM ENABLE: OPEN=OFF,Connector_PinHeader_2.54mm:PinHeader_1x02_P2.54mm_Vertical,,,,Fit header; leave shunt REMOVED by default
R25,4.7k 1%,Resistor_SMD:R_0805_2012Metric,,,I2C pull-up to 3.3V only,Fit
R26,4.7k 1%,Resistor_SMD:R_0805_2012Metric,,,I2C pull-up to 3.3V only,Fit
R27,10k 1%,Resistor_SMD:R_0805_2012Metric,,,Encoder pull-up; mechanical contact or 3.3V/open drain,Fit
R28,10k 1%,Resistor_SMD:R_0805_2012Metric,,,Encoder pull-up,Fit
R29,10k 1%,Resistor_SMD:R_0805_2012Metric,,,Open-drain 3.3V fault/IRQ pull-up,Fit
R30,330R 1%,Resistor_SMD:R_0805_2012Metric,,,Non-safety EN series damping/current limiting,Fit
R31,10k 1%,Resistor_SMD:R_0805_2012Metric,,,EN default low; not STO,Fit
R32,330R 1%,Resistor_SMD:R_0805_2012Metric,,,PWM control output series damping,Fit
R33,10k 1%,Resistor_SMD:R_0805_2012Metric,,,Haptic1 default low when unpowered/high-Z,Fit
R34,330R 1%,Resistor_SMD:R_0805_2012Metric,,,PWM control output series damping,Fit
R35,10k 1%,Resistor_SMD:R_0805_2012Metric,,,Haptic2 default low when unpowered/high-Z,Fit
R36,10k 1%,Resistor_SMD:R_0805_2012Metric,,,OE high disables outputs with default MODE2,Fit
R37,10k 1%,Resistor_SMD:R_0805_2012Metric,,,Future GP10 mode input; current firmware uses unexposed GP14,Fit
C5,100nF 16V X7R,Capacitor_SMD:C_0805_2012Metric,,,U2 local decoupling,Fit
C6,100nF 16V X7R,Capacitor_SMD:C_0805_2012Metric,,,U3 local decoupling,Fit
C7,4.7uF 10V X7R,Capacitor_SMD:C_0805_2012Metric,,,Logic rail bulk decoupling,Fit
C8,4.7uF 10V X7R,Capacitor_SMD:C_0805_2012Metric,,,Sensor branch bulk decoupling,Fit
C9,100nF 16V X7R,Capacitor_SMD:C_0805_2012Metric,,,Sensor branch HF decoupling,Fit
F1,PTC 0.25A hold,Fuse:Fuse_1206_3216Metric,Bourns,MF-NSMF025X-2,"Sensor branch short-circuit mitigation, not accurate current limiting",Fit
H1,M3 NPTH,MountingHole:MountingHole_3.2mm_M3,,,Mechanical mounting hole,Fit
H2,M3 NPTH,MountingHole:MountingHole_3.2mm_M3,,,Mechanical mounting hole,Fit
H3,M3 NPTH,MountingHole:MountingHole_3.2mm_M3,,,Mechanical mounting hole,Fit
H4,M3 NPTH,MountingHole:MountingHole_3.2mm_M3,,,Mechanical mounting hole,Fit

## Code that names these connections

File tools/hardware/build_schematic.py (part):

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    resistor(27,'10k 1%','+3V3','ENC_A','Encoder pull-up; mechanical contact or 3.3V/open drain')
    resistor(28,'10k 1%','+3V3','ENC_B','Encoder pull-up')
    resistor(29,'10k 1%','+3V3','FFB_IRQ_N','Open-drain 3.3V fault/IRQ pull-up')
    resistor(30,'330R 1%','FFB_EN_MCU','FFB_EN','Non-safety EN series damping/current limiting')
    resistor(31,'10k 1%','FFB_EN','GND','EN default low; not STO')
    resistor(32,'330R 1%','PWM0_RAW','HAPTIC1','PWM control output series damping')
    resistor(33,'10k 1%','HAPTIC1','GND','Haptic1 default low when unpowered/high-Z')
    resistor(34,'330R 1%','PWM1_RAW','HAPTIC2','PWM control output series damping')
    resistor(35,'10k 1%','HAPTIC2','GND','Haptic2 default low when unpowered/high-Z')
    resistor(36,'10k 1%','+3V3','PWM_OE_N','OE high disables outputs with default MODE2')
    resistor(37,'10k 1%','+3V3','MODE_N','Future GP10 mode input; current firmware uses unexposed GP14')
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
